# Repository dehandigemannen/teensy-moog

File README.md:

# Teensymoog board[untested]
> Simple board to provide inputs for the teensy audio library

## Components
A list of components can be found [here](https://docs.google.com/spreadsheets/d/1O3fiJveS2LG4Vu1J4wDSkKv0wMXK735ehudC7_bgVOY/edit?usp=sharing)

> This board uses the teensy 3.6 board with build-in dac, the next version of the board should work with the teensy 4.1 because of the shortage of the 3.6 teensy.

## Preview

## Rev2

- [] Connect switches to 3.3 V instead of ground.
- [] Create multiple boards to compensate for hight difference of pots and switches
- [] Use toggle switches that are on / of

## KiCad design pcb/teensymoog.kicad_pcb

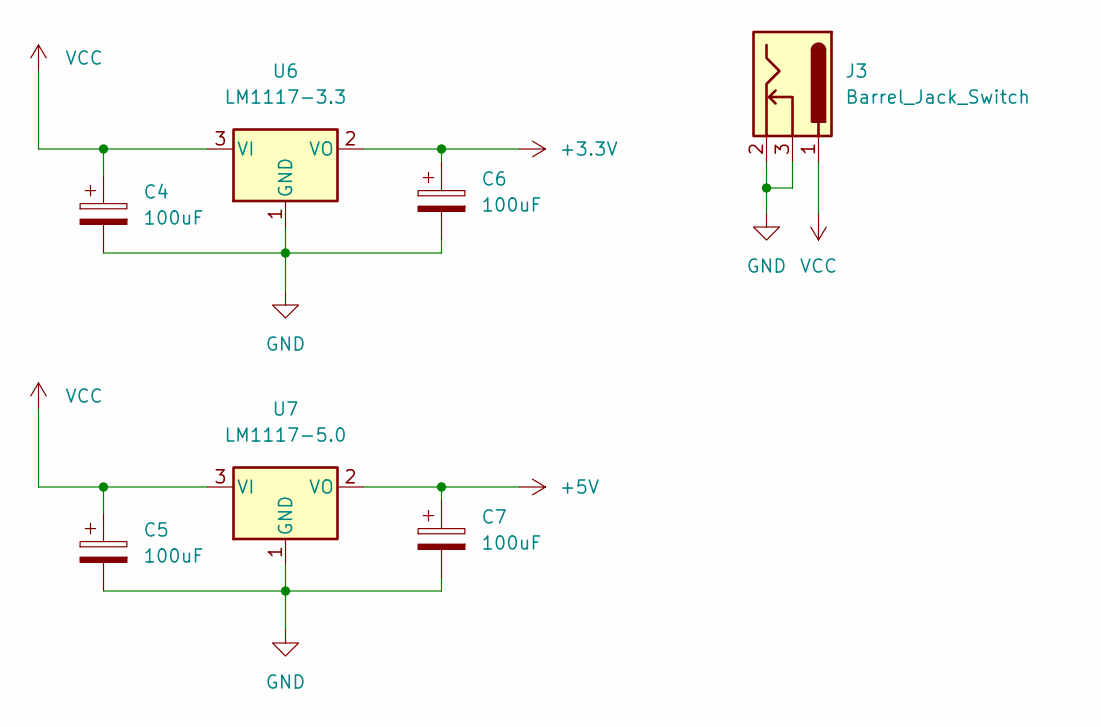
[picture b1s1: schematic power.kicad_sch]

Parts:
C4, C5, C6, C7: 100uF; CP_Radial_D6.3mm_P2.50mm
J3: Barrel_Jack_Switch; BarrelJack_Horizontal
U6: LM1117-3.3; TO-220-3_Vertical
U7: LM1117-5.0; TO-220-3_Vertical

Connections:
+3V3: C6.1, U6.2 (VO); also elsewhere on the board
+5V: C7.1, U7.2 (VO); also elsewhere on the board
GND: C4.2, C5.2, C6.2, C7.2, J3.2, J3.3, U6.1 (GND), U7.1 (GND); also elsewhere on the board
VCC: C4.1, C5.1, J3.1, U6.3 (VI), U7.3 (VI)

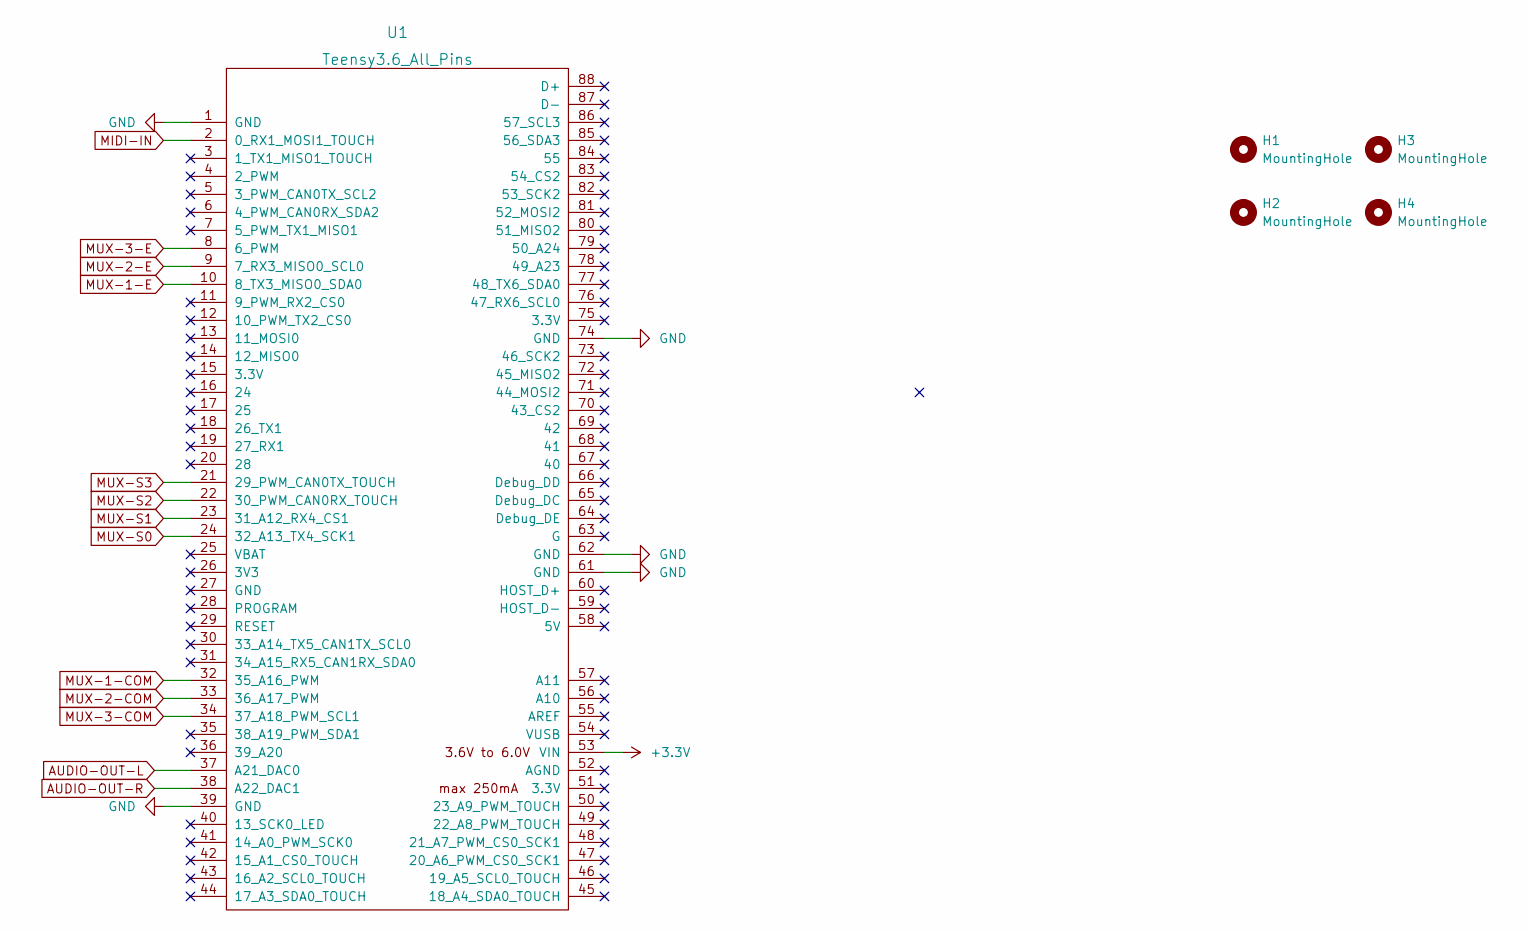
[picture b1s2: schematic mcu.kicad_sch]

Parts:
H1, H2, H3, H4: MountingHole; MountingHole_4.3mm_M4_DIN965
U1: Teensy3.6_All_Pins; Teensy35_36_All_Pins

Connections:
+3V3: U1.53 (VIN); also elsewhere on the board
AUDIO-OUT-L: U1.37 (A21_DAC0); also elsewhere on the board
AUDIO-OUT-R: U1.38 (A22_DAC1); also elsewhere on the board
GND: U1.1 (GND), U1.39 (GND), U1.61 (GND), U1.62 (GND), U1.74 (GND); also elsewhere on the board
MIDI-IN: U1.2 (0_RX1_MOSI1_TOUCH); also elsewhere on the board
MUX-1-COM: U1.32 (35_A16_PWM); also elsewhere on the board
MUX-1-E: U1.10 (8_TX3_MISO0_SDA0); also elsewhere on the board
MUX-2-COM: U1.33 (36_A17_PWM); also elsewhere on the board
MUX-2-E: U1.9 (7_RX3_MISO0_SCL0); also elsewhere on the board
MUX-3-COM: U1.34 (37_A18_PWM_SCL1); also elsewhere on the board
MUX-3-E: U1.8 (6_PWM); also elsewhere on the board
MUX-S0: U1.24 (32_A13_TX4_SCK1); also elsewhere on the board
MUX-S1: U1.23 (31_A12_RX4_CS1); also elsewhere on the board
MUX-S2: U1.22 (30_PWM_CAN0RX_TOUCH); also elsewhere on the board
MUX-S3: U1.21 (29_PWM_CAN0TX_TOUCH); also elsewhere on the board

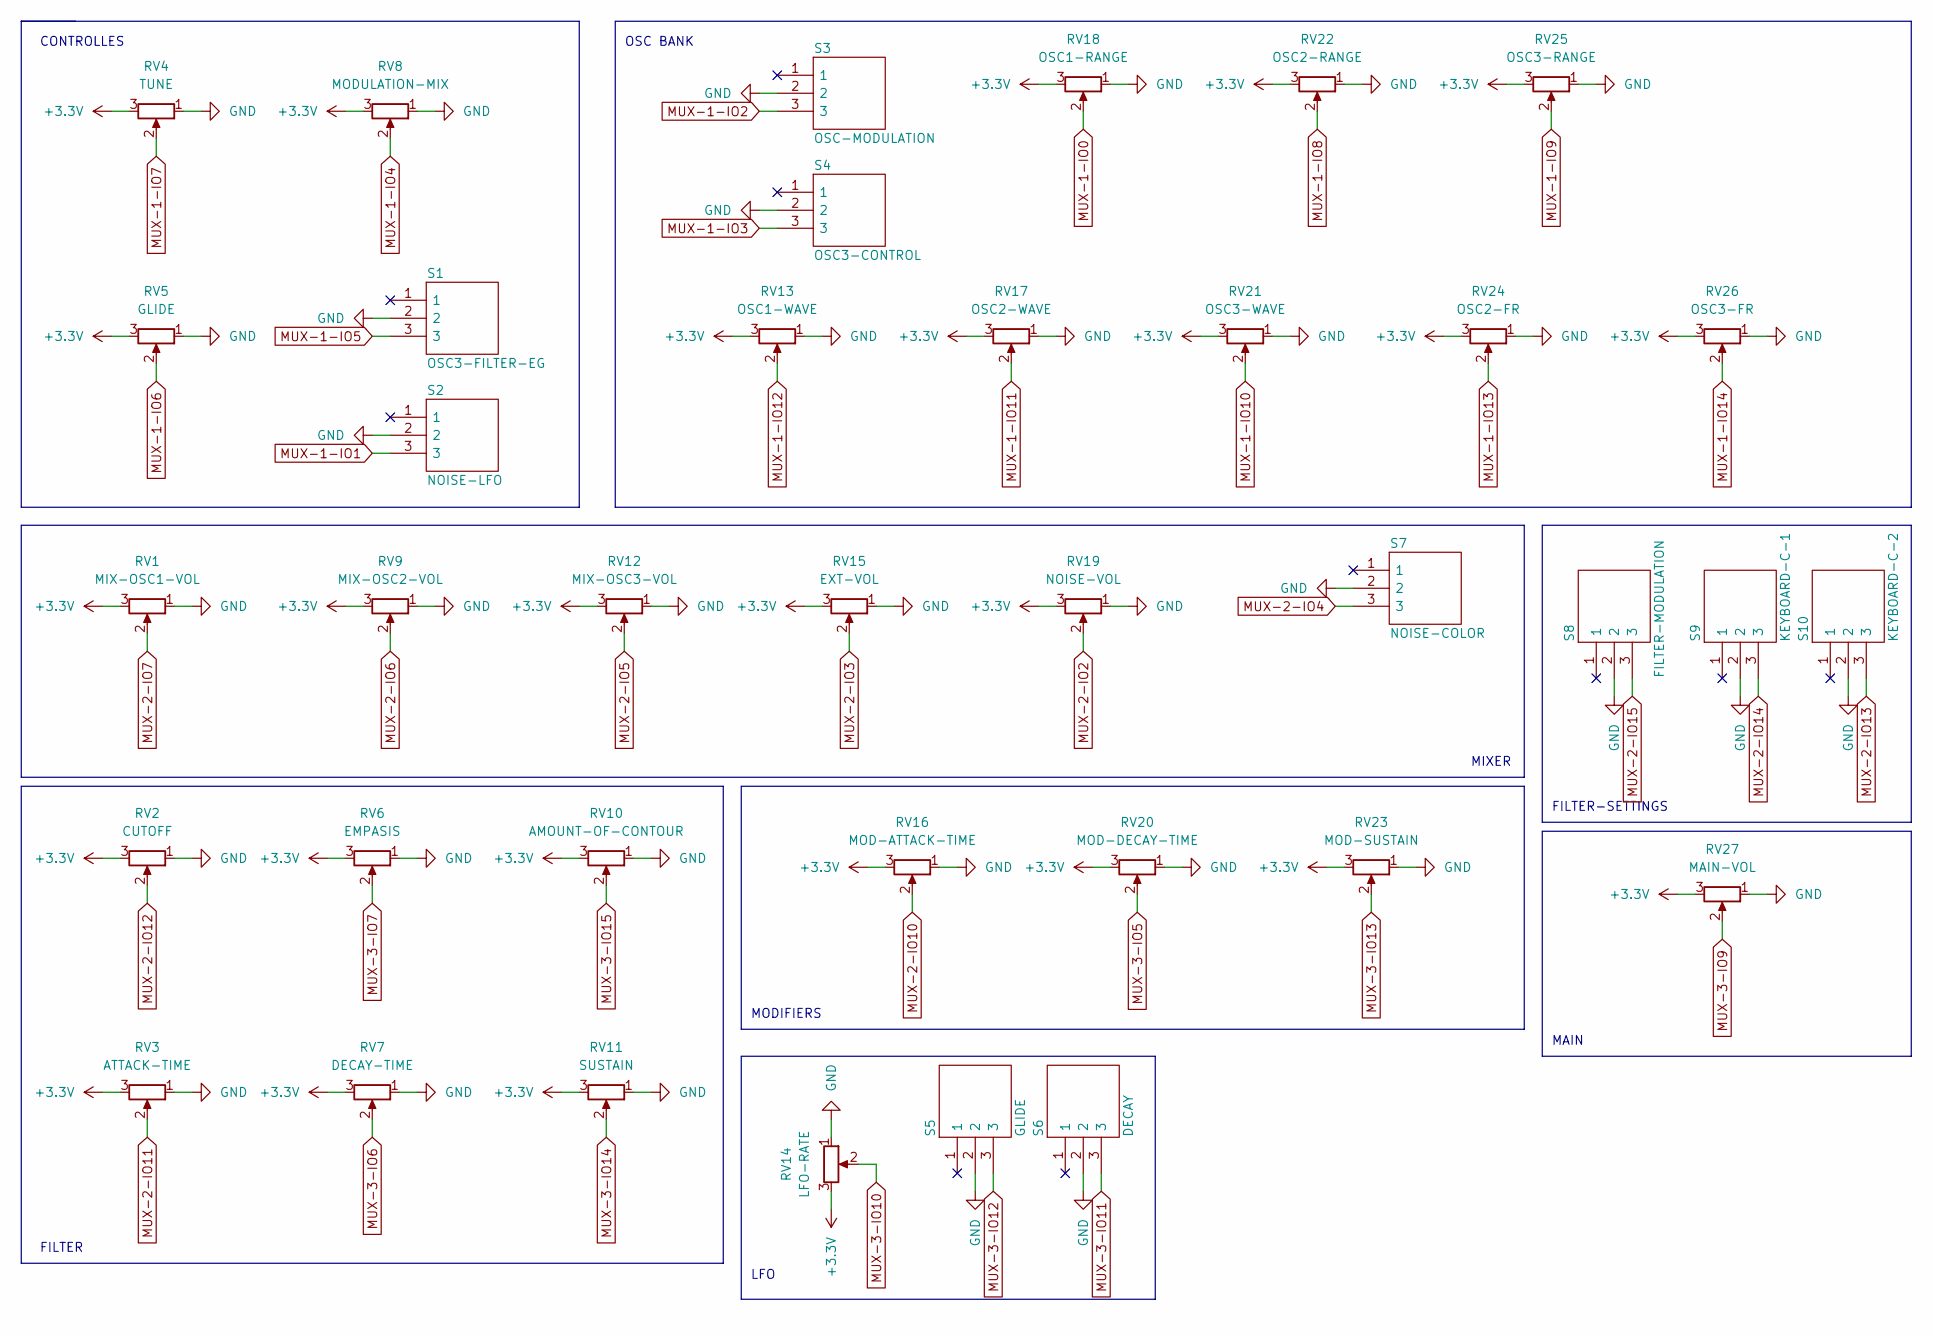
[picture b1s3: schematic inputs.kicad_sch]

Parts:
RV1: MIX-OSC1-VOL; Potentiometer_Alps_RK09K_Single_Vertical
RV2: CUTOFF; Potentiometer_Alps_RK09K_Single_Vertical
RV3: ATTACK-TIME; Potentiometer_Alps_RK09K_Single_Vertical
RV4: TUNE; Potentiometer_Alps_RK09K_Single_Vertical
RV5: GLIDE; Potentiometer_Alps_RK09K_Single_Vertical
RV6: EMPASIS; Potentiometer_Alps_RK09K_Single_Vertical
RV7: DECAY-TIME; Potentiometer_Alps_RK09K_Single_Vertical
RV8: MODULATION-MIX; Potentiometer_Alps_RK09K_Single_Vertical
RV9: MIX-OSC2-VOL; Potentiometer_Alps_RK09K_Single_Vertical
RV10: AMOUNT-OF-CONTOUR; Potentiometer_Alps_RK09K_Single_Vertical
RV11: SUSTAIN; Potentiometer_Alps_RK09K_Single_Vertical
RV12: MIX-OSC3-VOL; Potentiometer_Alps_RK09K_Single_Vertical
RV13: OSC1-WAVE; Potentiometer_Alps_RK09K_Single_Vertical
RV14: LFO-RATE; Potentiometer_Alps_RK09K_Single_Vertical
RV15: EXT-VOL; Potentiometer_Alps_RK09K_Single_Vertical
RV16: MOD-ATTACK-TIME; Potentiometer_Alps_RK09K_Single_Vertical
RV17: OSC2-WAVE; Potentiometer_Alps_RK09K_Single_Vertical
RV18: OSC1-RANGE; Potentiometer_Alps_RK09K_Single_Vertical
RV19: NOISE-VOL; Potentiometer_Alps_RK09K_Single_Vertical
RV20: MOD-DECAY-TIME; Potentiometer_Alps_RK09K_Single_Vertical
RV21: OSC3-WAVE; Potentiometer_Alps_RK09K_Single_Vertical
RV22: OSC2-RANGE; Potentiometer_Alps_RK09K_Single_Vertical
RV23: MOD-SUSTAIN; Potentiometer_Alps_RK09K_Single_Vertical
RV24: OSC2-FR; Potentiometer_Alps_RK09K_Single_Vertical
RV25: OSC3-RANGE; Potentiometer_Alps_RK09K_Single_Vertical
RV26: OSC3-FR; Potentiometer_Alps_RK09K_Single_Vertical
RV27: MAIN-VOL; Potentiometer_Alps_RK09K_Single_Vertical
S1: OSC3-FILTER-EG; 2M1SP3T1B1M2QE; Manufacturer_Part_Number 2M1-SP1-T1-B1-M2QE; Mouser Part Number 691-2M1-SP1-T1B1M2QE
S2: NOISE-LFO; 2M1SP3T1B1M2QE; Manufacturer_Part_Number 2M1-SP1-T1-B1-M2QE; Mouser Part Number 691-2M1-SP1-T1B1M2QE
S3: OSC-MODULATION; 2M1SP3T1B1M2QE; Manufacturer_Part_Number 2M1-SP1-T1-B1-M2QE; Mouser Part Number 691-2M1-SP1-T1B1M2QE
S4: OSC3-CONTROL; 2M1SP3T1B1M2QE; Manufacturer_Part_Number 2M1-SP1-T1-B1-M2QE; Mouser Part Number 691-2M1-SP1-T1B1M2QE
S5: GLIDE; 2M1SP3T1B1M2QE; Manufacturer_Part_Number 2M1-SP1-T1-B1-M2QE; Mouser Part Number 691-2M1-SP1-T1B1M2QE
S6: DECAY; 2M1SP3T1B1M2QE; Manufacturer_Part_Number 2M1-SP1-T1-B1-M2QE; Mouser Part Number 691-2M1-SP1-T1B1M2QE
S7: NOISE-COLOR; 2M1SP3T1B1M2QE; Manufacturer_Part_Number 2M1-SP1-T1-B1-M2QE; Mouser Part Number 691-2M1-SP1-T1B1M2QE
S8: FILTER-MODULATION; 2M1SP3T1B1M2QE; Manufacturer_Part_Number 2M1-SP1-T1-B1-M2QE; Mouser Part Number 691-2M1-SP1-T1B1M2QE
S9: KEYBOARD-C-1; 2M1SP3T1B1M2QE; Manufacturer_Part_Number 2M1-SP1-T1-B1-M2QE; Mouser Part Number 691-2M1-SP1-T1B1M2QE
S10: KEYBOARD-C-2; 2M1SP3T1B1M2QE; Manufacturer_Part_Number 2M1-SP1-T1-B1-M2QE; Mouser Part Number 691-2M1-SP1-T1B1M2QE

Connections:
+3V3: RV1.3, RV2.3, RV3.3, RV4.3, RV5.3, RV6.3, RV7.3, RV8.3, RV9.3, RV10.3, RV11.3, RV12.3, RV13.3, RV14.3, RV15.3, RV16.3, RV17.3, RV18.3, RV19.3, RV20.3, RV21.3, RV22.3, RV23.3, RV24.3, RV25.3, RV26.3, RV27.3; also elsewhere on the board
GND: RV1.1, RV2.1, RV3.1, RV4.1, RV5.1, RV6.1, RV7.1, RV8.1, RV9.1, RV10.1, RV11.1, RV12.1, RV13.1, RV14.1, RV15.1, RV16.1, RV17.1, RV18.1, RV19.1, RV20.1, RV21.1, RV22.1, RV23.1, RV24.1, RV25.1, RV26.1, RV27.1, S1.2, S2.2, S3.2, S4.2, S5.2, S6.2, S7.2, S8.2, S9.2, S10.2; also elsewhere on the board
MUX-1-IO0: RV18.2; also elsewhere on the board
MUX-1-IO1: S2.3; also elsewhere on the board
MUX-1-IO2: S3.3; also elsewhere on the board
MUX-1-IO3: S4.3; also elsewhere on the board
MUX-1-IO4: RV8.2; also elsewhere on the board
MUX-1-IO5: S1.3; also elsewhere on the board
MUX-1-IO6: RV5.2; also elsewhere on the board
MUX-1-IO7: RV4.2; also elsewhere on the board
MUX-1-IO8: RV22.2; also elsewhere on the board
MUX-1-IO9: RV25.2; also elsewhere on the board
MUX-1-IO10: RV21.2; also elsewhere on the board
MUX-1-IO11: RV17.2; also elsewhere on the board
MUX-1-IO12: RV13.2; also elsewhere on the board
MUX-1-IO13: RV24.2; also elsewhere on the board
MUX-1-IO14: RV26.2; also elsewhere on the board
MUX-2-IO2: RV19.2; also elsewhere on the board
MUX-2-IO3: RV15.2; also elsewhere on the board
MUX-2-IO4: S7.3; also elsewhere on the board
MUX-2-IO5: RV12.2; also elsewhere on the board
MUX-2-IO6: RV9.2; also elsewhere on the board
MUX-2-IO7: RV1.2; also elsewhere on the board
MUX-2-IO10: RV16.2; also elsewhere on the board
MUX-2-IO11: RV3.2; also elsewhere on the board
MUX-2-IO12: RV2.2; also elsewhere on the board
MUX-2-IO13: S10.3; also elsewhere on the board
MUX-2-IO14: S9.3; also elsewhere on the board
MUX-2-IO15: S8.3; also elsewhere on the board
MUX-3-IO5: RV20.2; also elsewhere on the board
MUX-3-IO6: RV7.2; also elsewhere on the board
MUX-3-IO7: RV6.2; also elsewhere on the board
MUX-3-IO9: RV27.2; also elsewhere on the board
MUX-3-IO10: RV14.2; also elsewhere on the board
MUX-3-IO11: S6.3; also elsewhere on the board
MUX-3-IO12: S5.3; also elsewhere on the board
MUX-3-IO13: RV23.2; also elsewhere on the board
MUX-3-IO14: RV11.2; also elsewhere on the board
MUX-3-IO15: RV10.2; also elsewhere on the board

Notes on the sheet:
MIXER
MODIFIERS
FILTER-SETTINGS
LFO
OSC BANK
CONTROLLES
MAIN
FILTER

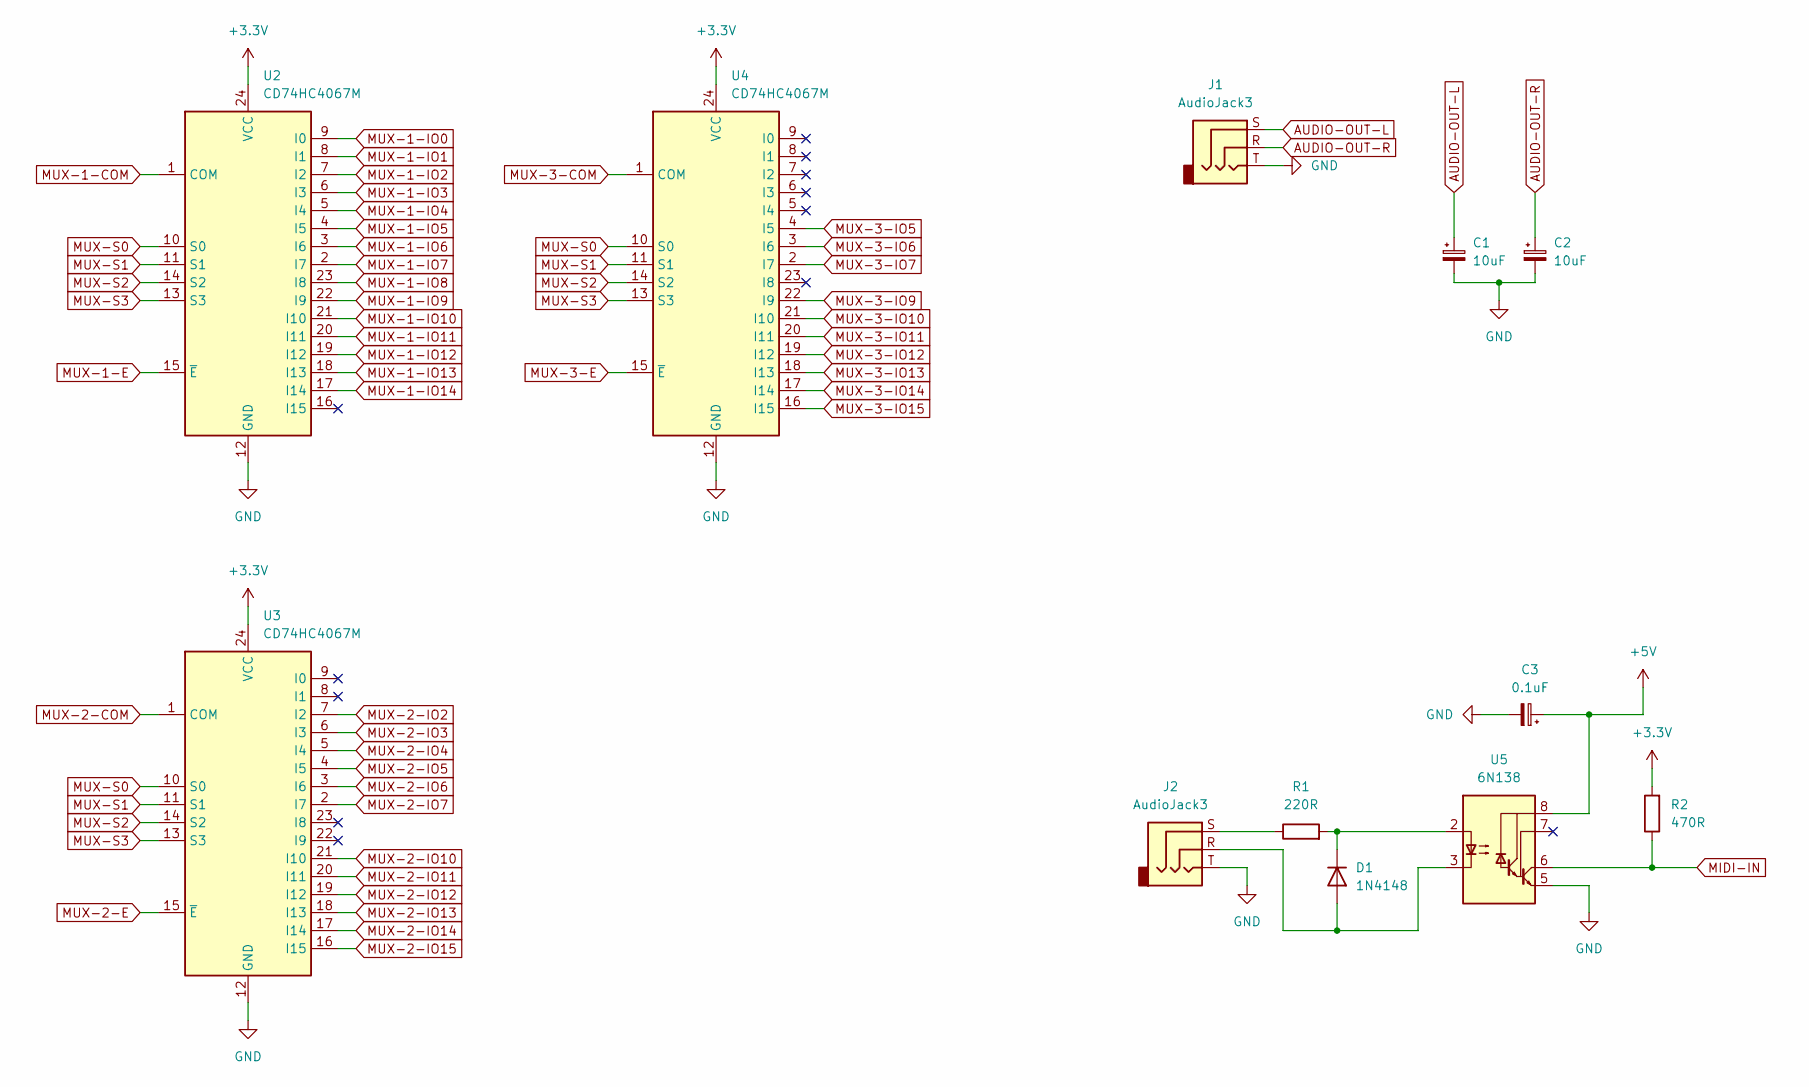
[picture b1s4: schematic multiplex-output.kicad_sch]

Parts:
C1, C2: 10uF; CP_Radial_D6.3mm_P2.50mm
C3: 0.1uF; CP_Radial_D6.3mm_P2.50mm
D1: 1N4148; D_DO-35_SOD27_P7.62mm_Horizontal
J1, J2: AudioJack3; Jack_3.5mm_CUI_SJ1-3533NG_Horizontal
R1: 220R; R_0805_2012Metric_Pad1.20x1.40mm_HandSolder
R2: 470R; R_0805_2012Metric_Pad1.20x1.40mm_HandSolder
U2, U3, U4: CD74HC4067M; SOIC-24W_7.5x15.4mm_P1.27mm
U5: 6N138; DIP-8_W7.62mm_LongPads

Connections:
+3V3: R2.2, U2.24 (VCC), U3.24 (VCC), U4.24 (VCC); also elsewhere on the board
+5V: C3.1, U5.8 (VCC); also elsewhere on the board
AUDIO-OUT-L: C1.1, J1.S; also elsewhere on the board
AUDIO-OUT-R: C2.1, J1.R; also elsewhere on the board
GND: C1.2, C2.2, C3.2, J1.T, J2.T, U2.12 (GND), U3.12 (GND), U4.12 (GND), U5.5 (GND); also elsewhere on the board
MIDI-IN: R2.1, U5.6 (VO2); also elsewhere on the board
MUX-1-COM: U2.1 (COM); also elsewhere on the board
MUX-1-E: U2.15 (~E); also elsewhere on the board
MUX-1-IO0: U2.9 (I0); also elsewhere on the board
MUX-1-IO1: U2.8 (I1); also elsewhere on the board
MUX-1-IO2: U2.7 (I2); also elsewhere on the board
MUX-1-IO3: U2.6 (I3); also elsewhere on the board
MUX-1-IO4: U2.5 (I4); also elsewhere on the board
MUX-1-IO5: U2.4 (I5); also elsewhere on the board
MUX-1-IO6: U2.3 (I6); also elsewhere on the board
MUX-1-IO7: U2.2 (I7); also elsewhere on the board
MUX-1-IO8: U2.23 (I8); also elsewhere on the board
MUX-1-IO9: U2.22 (I9); also elsewhere on the board
MUX-1-IO10: U2.21 (I10); also elsewhere on the board
MUX-1-IO11: U2.20 (I11); also elsewhere on the board
MUX-1-IO12: U2.19 (I12); also elsewhere on the board
MUX-1-IO13: U2.18 (I13); also elsewhere on the board
MUX-1-IO14: U2.17 (I14); also elsewhere on the board
MUX-2-COM: U3.1 (COM); also elsewhere on the board
MUX-2-E: U3.15 (~E); also elsewhere on the board
MUX-2-IO2: U3.7 (I2); also elsewhere on the board
MUX-2-IO3: U3.6 (I3); also elsewhere on the board
MUX-2-IO4: U3.5 (I4); also elsewhere on the board
MUX-2-IO5: U3.4 (I5); also elsewhere on the board
MUX-2-IO6: U3.3 (I6); also elsewhere on the board
MUX-2-IO7: U3.2 (I7); also elsewhere on the board
MUX-2-IO10: U3.21 (I10); also elsewhere on the board
MUX-2-IO11: U3.20 (I11); also elsewhere on the board
MUX-2-IO12: U3.19 (I12); also elsewhere on the board
MUX-2-IO13: U3.18 (I13); also elsewhere on the board
MUX-2-IO14: U3.17 (I14); also elsewhere on the board
MUX-2-IO15: U3.16 (I15); also elsewhere on the board
MUX-3-COM: U4.1 (COM); also elsewhere on the board
MUX-3-E: U4.15 (~E); also elsewhere on the board
MUX-3-IO5: U4.4 (I5); also elsewhere on the board
MUX-3-IO6: U4.3 (I6); also elsewhere on the board
MUX-3-IO7: U4.2 (I7); also elsewhere on the board
MUX-3-IO9: U4.22 (I9); also elsewhere on the board
MUX-3-IO10: U4.21 (I10); also elsewhere on the board
MUX-3-IO11: U4.20 (I11); also elsewhere on the board
MUX-3-IO12: U4.19 (I12); also elsewhere on the board
MUX-3-IO13: U4.18 (I13); also elsewhere on the board
MUX-3-IO14: U4.17 (I14); also elsewhere on the board
MUX-3-IO15: U4.16 (I15); also elsewhere on the board
MUX-S0: U2.10 (S0), U3.10 (S0), U4.10 (S0); also elsewhere on the board
MUX-S1: U2.11 (S1), U3.11 (S1), U4.11 (S1); also elsewhere on the board
MUX-S2: U2.14 (S2), U3.14 (S2), U4.14 (S2); also elsewhere on the board
MUX-S3: U2.13 (S3), U3.13 (S3), U4.13 (S3); also elsewhere on the board
unnamed: D1.1 (K), R1.2, U5.2 (C1)
unnamed: D1.2 (A), J2.R, U5.3 (C2)
unnamed: J2.S, R1.1

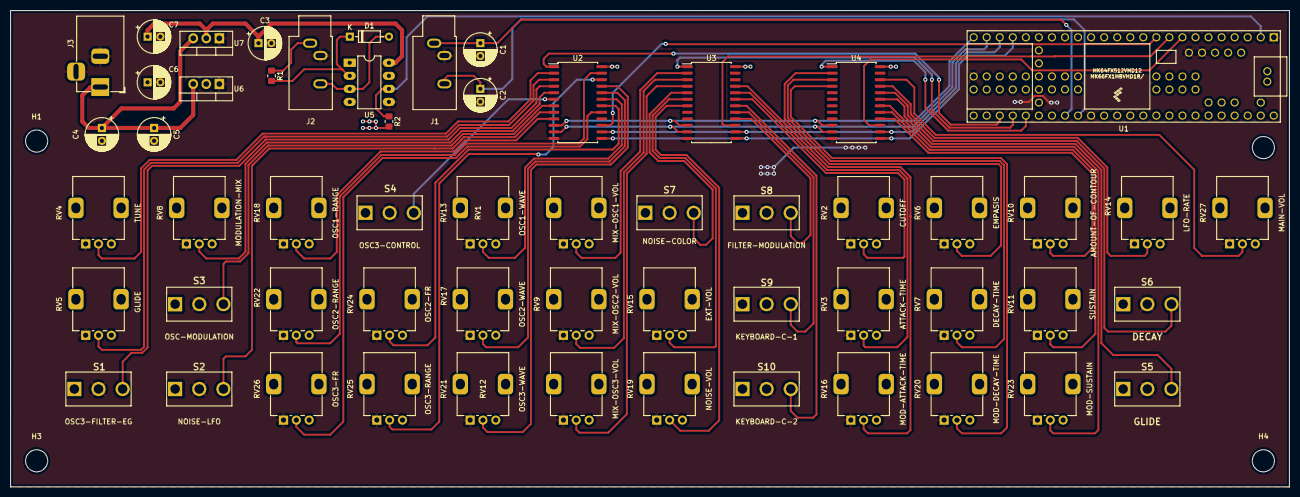
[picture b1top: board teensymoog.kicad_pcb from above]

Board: 2 copper layers, 248.9 x 92.7 mm, 61 parts (0 on the bottom side), 57 nets.

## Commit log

2023-01-18 Add first version of the pcb
2023-01-18 Add markdown readme
2023-01-22 Move files to pcb folder
2023-01-22 Add first setup for hc4067 chip
2023-01-27 Fix bug with select pins and inverted enable pin
2023-01-27 Read all the pins and log to Serial
2023-01-29 Add code for reading all inputs
2023-01-30 Remove unused helpers.
